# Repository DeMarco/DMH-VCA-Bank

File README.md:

# DMH-VCA-Bank
Another attempt at multiple VCAs in a small module

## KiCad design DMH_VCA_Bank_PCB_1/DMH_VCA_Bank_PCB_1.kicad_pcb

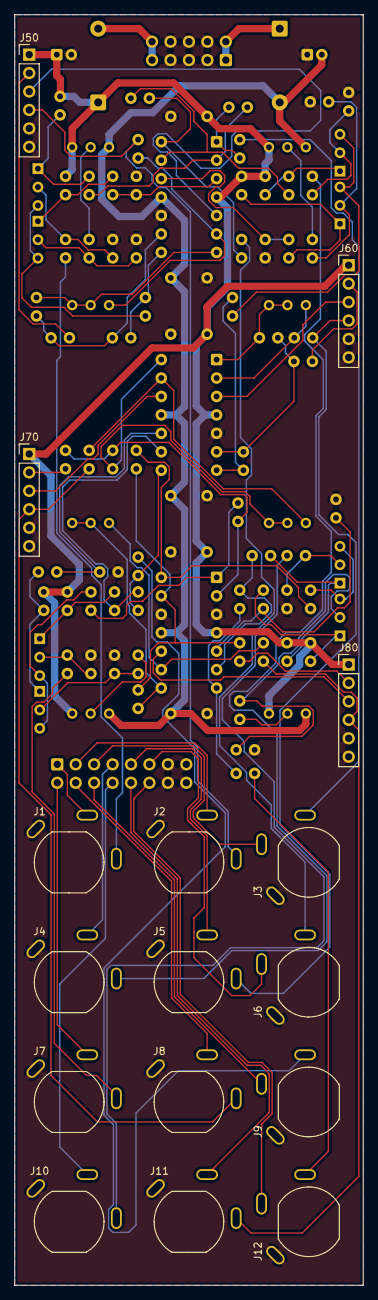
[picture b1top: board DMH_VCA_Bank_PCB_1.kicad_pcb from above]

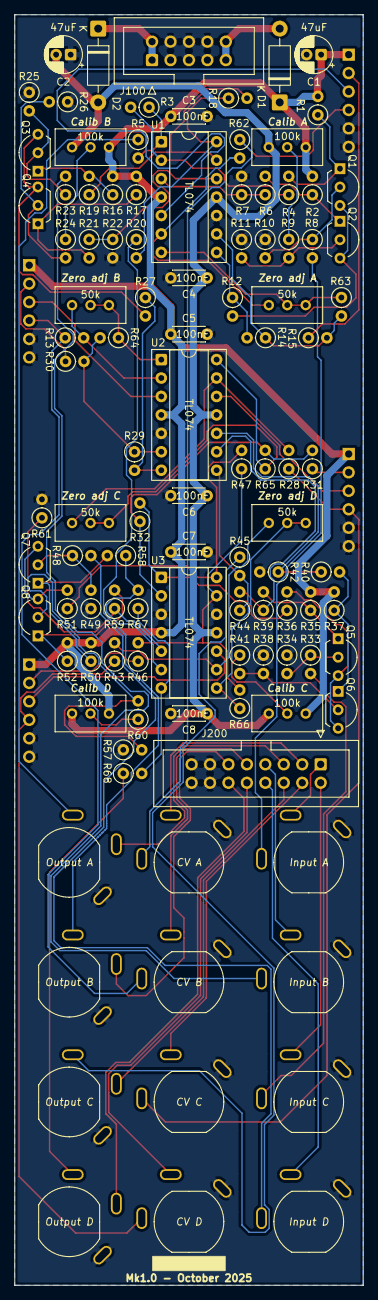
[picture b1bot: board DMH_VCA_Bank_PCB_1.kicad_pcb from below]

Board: 2 copper layers, 48.0 x 175.0 mm, 111 parts (95 on the bottom side), 89 nets.

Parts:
C1, C2: 47uF; CP_Radial_D5.0mm_P2.00mm
C3, C4, C5, C6, C7, C8: 100nF; C_Disc_D4.3mm_W1.9mm_P5.00mm
D1, D2: SB140; D_DO-41_SOD81_P10.16mm_Horizontal
J1, J2, J3, J4, J5, J6, J7, J8, J9, J10, J11, J12: TS_Jack_6.35mm_Sw; CUI_MJ-63052A
J50, J60, J70, J80: Conn_01x06; PinHeader_1x06_P2.54mm_Vertical
J100: IDC_02x05; IDC-Header_2x05_P2.54mm_Vertical_Eurorack
J200: IDC_02x08; IDC-Header_2x08_P2.54mm_Vertical_BackBone
Q1, Q2, Q3, Q4, Q5, Q6, Q7, Q8: BC548; TO-92L_Inline_Wide
R1, R2, R16, R17, R35, R37, R50, R52: 20k; R_Axial_DIN0207_L6.3mm_D2.5mm_P2.54mm_Vertical
R3, R7, R8, R9, R14, R15, R18, R22, R23, R24, R29, R30, R31, R32, R33, R41, R42, R44, R46, R47, R48, R60, R61, R63, R64, R65, R66, R67: 100k; R_Axial_DIN0207_L6.3mm_D2.5mm_P2.54mm_Vertical
R4, R6, R12, R19, R21, R27, R36, R39, R40, R51, R58, R59: 10k; R_Axial_DIN0207_L6.3mm_D2.5mm_P2.54mm_Vertical
R5, R20, R45, R68: 1k; R_Axial_DIN0207_L6.3mm_D2.5mm_P2.54mm_Vertical
R10, R11, R25, R26, R34, R38, R49, R57: 100R; R_Axial_DIN0207_L6.3mm_D2.5mm_P2.54mm_Vertical
R13, R28, R43, R62: 33k; R_Axial_DIN0207_L6.3mm_D2.5mm_P2.54mm_Vertical
RV1, RV2, RV3, RV16: 100k; Potentiometer_Bourns_3296W_Vertical
RV10, RV11, RV12, RV15: 50k; Potentiometer_Bourns_3296W_Vertical
U1, U2, U3: TL074; DIP-14_W7.62mm_Socket

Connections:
+12V: C1.1, C3.1, C5.1, C7.1, D1.1 (K), J50.1, J60.1, J70.1, J80.1, R1.2, R2.2, R16.2, R17.2, R35.2, R37.2, R50.2, R52.2, RV1.3, RV2.3, RV3.3, RV16.3, U1.4 (V+), U2.4 (V+), U3.4 (V+)
-12V: C2.2, C4.2, C6.2, C8.2, D2.2 (A), RV1.1, RV2.1, RV3.1, RV16.1, U1.11 (V-), U2.11 (V-), U3.11 (V-)
/Inputs and Outputs/CV A Jack: J2.T, J50.4, R62.1
/Inputs and Outputs/CV Amt A Pot: J50.3, U1.5 (+)
/Inputs and Outputs/CV Amt B Pot: J60.3, U2.3 (+)
/Inputs and Outputs/CV Amt C Pot: J70.3, U2.12 (+)
/Inputs and Outputs/CV Amt D Pot: J80.3, U3.10 (+)
/Inputs and Outputs/CV B Jack: J5.T, J60.4, R13.1
/Inputs and Outputs/CV C Jack: J8.T, J70.4, R28.1
/Inputs and Outputs/CV D Jack: J11.T, J80.4, R43.1
/Inputs and Outputs/Input A Jack: J1.T, R8.2
/Inputs and Outputs/Input B Jack: J4.T, R23.2
/Inputs and Outputs/Input C Jack: J7.T, R33.2
/Inputs and Outputs/Input D Jack: J10.T, R48.2
/Inputs and Outputs/Offset A Pot: J50.2, R15.1
/Inputs and Outputs/Offset B Pot: J60.2, R30.1
/Inputs and Outputs/Offset C Pot: J70.2, R31.1
/Inputs and Outputs/Offset D Pot: J80.2, R46.1
/Inputs and Outputs/Output A Jack: J3.T, R5.1
/Inputs and Outputs/Output B Jack: J6.T, R20.1
/Inputs and Outputs/Output C Jack: J9.T, R45.1
/Inputs and Outputs/Output D Jack: J12.T, R68.1
GND: C1.2, C2.1, C3.2, C4.1, C5.2, C6.1, C7.2, C8.1, J1.S, J2.S, J3.S, J4.S, J5.S, J6.S, J7.S, J8.S, J9.S, J10.S, J11.S, J12.S, J50.5, J50.6, J60.5, J60.6, J70.5, J70.6, J80.5, J80.6, J100.2a, J100.2b, J100.3a, J100.3b, J100.4a, J100.4b, J200.7, J200.8, J200.15, J200.16, R7.2, R10.1, R11.1, R22.2, R25.1, R26.1, R34.1, R38.1, R42.2, R49.1, R57.1, R61.2, U1.10 (+), U2.5 (+), U3.3 (+), U3.12 (+)
unnamed: D1.2 (A), J100.5a, J100.5b
unnamed: D2.1 (K), J100.1a, J100.1b
unnamed: J1.TN, J200.1
unnamed: J2.TN, J200.2
unnamed: J3.TN, J200.3
unnamed: J4.TN, J200.4
unnamed: J5.TN, J200.5
unnamed: J6.TN, J200.6
unnamed: J7.TN, J200.9
unnamed: J8.TN, J200.10
unnamed: J9.TN, J200.11
unnamed: J10.TN, J200.12
unnamed: J11.TN, J200.13
unnamed: J12.TN, J200.14
unnamed: Q1.2 (B), R8.1, R10.2
unnamed: Q1.1 (C), R1.1, R4.2
unnamed: Q1.3 (E), Q2.3 (E), R12.2
unnamed: Q2.2 (B), R9.2, R11.2
unnamed: Q2.1 (C), R2.1, R6.2
unnamed: Q3.2 (B), R23.1, R25.2
unnamed: Q3.1 (C), R16.1, R19.2
unnamed: Q3.3 (E), Q4.3 (E), R27.2
unnamed: Q4.2 (B), R24.2, R26.2
unnamed: Q4.1 (C), R17.1, R21.2
unnamed: Q5.2 (B), R33.1, R34.2
unnamed: Q5.1 (C), R35.1, R39.2
unnamed: Q5.3 (E), Q6.3 (E), R36.2
unnamed: Q6.2 (B), R38.2, R41.2
unnamed: Q6.1 (C), R37.1, R40.2
unnamed: Q7.2 (B), R48.1, R49.2
unnamed: Q7.1 (C), R50.1, R58.2
unnamed: Q7.3 (E), Q8.3 (E), R51.2
unnamed: Q8.2 (B), R57.2, R60.2
unnamed: Q8.1 (C), R52.1, R59.2
unnamed: R3.1, R5.2, U1.1
unnamed: R9.1, RV1.2
unnamed: R12.1, R14.2, U1.8
unnamed: R18.1, R20.2, U1.14
unnamed: R24.1, RV2.2
unnamed: R27.1, R29.2, U2.7
unnamed: R32.2, R36.1, U3.1
unnamed: R41.1, RV3.2
unnamed: R44.1, R45.2, U2.8
unnamed: R47.2, R51.1, U3.14
unnamed: R60.1, RV16.2
unnamed: R63.1, RV10.2, RV10.3, U1.7
unnamed: R64.1, RV11.2, RV11.3, U2.1
unnamed: R65.1, RV12.2, RV12.3, U2.14
unnamed: R66.1, RV15.2, RV15.3, U3.8
unnamed: R67.1, R68.2, U3.7
unnamed: R6.1, R7.1, U1.3 (+)
unnamed: R3.2, R4.1, U1.2 (-)
unnamed: R62.2, RV10.1, U1.6 (-)
unnamed: R14.1, R15.2, R63.2, U1.9 (-)
unnamed: R21.1, R22.1, U1.12 (+)
unnamed: R18.2, R19.1, U1.13 (-)
unnamed: R13.2, RV11.1, U2.2 (-)
unnamed: R29.1, R30.2, R64.2, U2.6 (-)
unnamed: R40.1, R42.1, U2.10 (+)
unnamed: R39.1, R44.2, U2.9 (-)
unnamed: R28.2, RV12.1, U2.13 (-)
unnamed: R31.2, R32.1, R65.2, U3.2 (-)
unnamed: R59.1, R61.1, U3.5 (+)
unnamed: R58.1, R67.2, U3.6 (-)
unnamed: R43.2, RV15.1, U3.9 (-)
unnamed: R46.2, R47.1, R66.2, U3.13 (-)

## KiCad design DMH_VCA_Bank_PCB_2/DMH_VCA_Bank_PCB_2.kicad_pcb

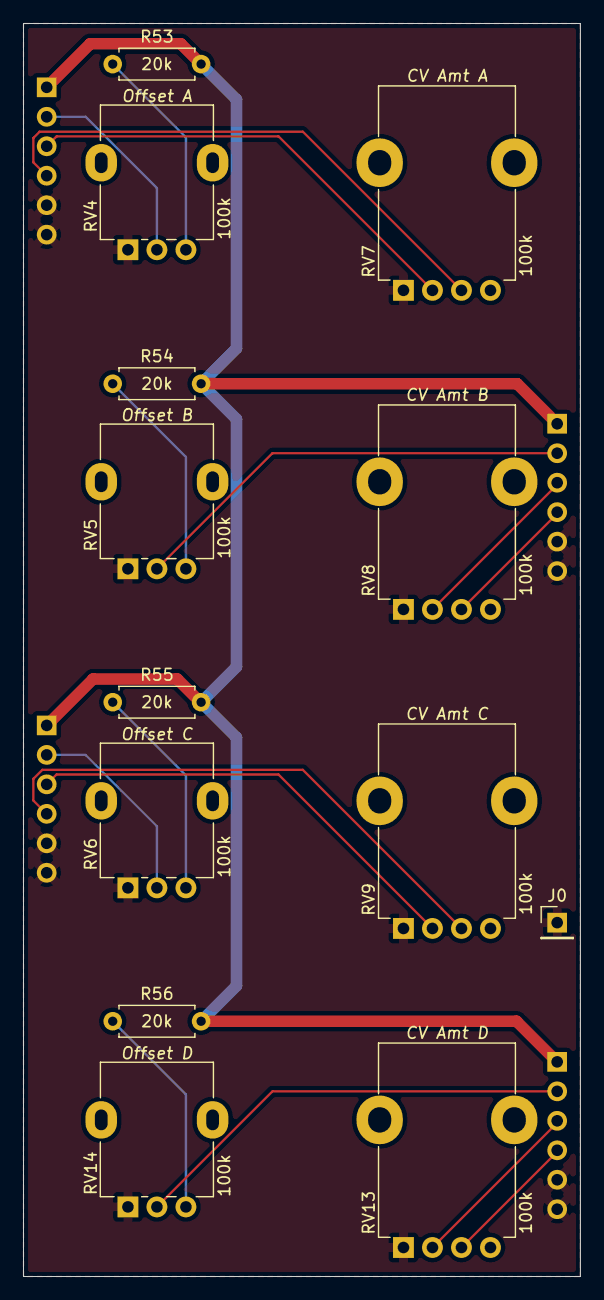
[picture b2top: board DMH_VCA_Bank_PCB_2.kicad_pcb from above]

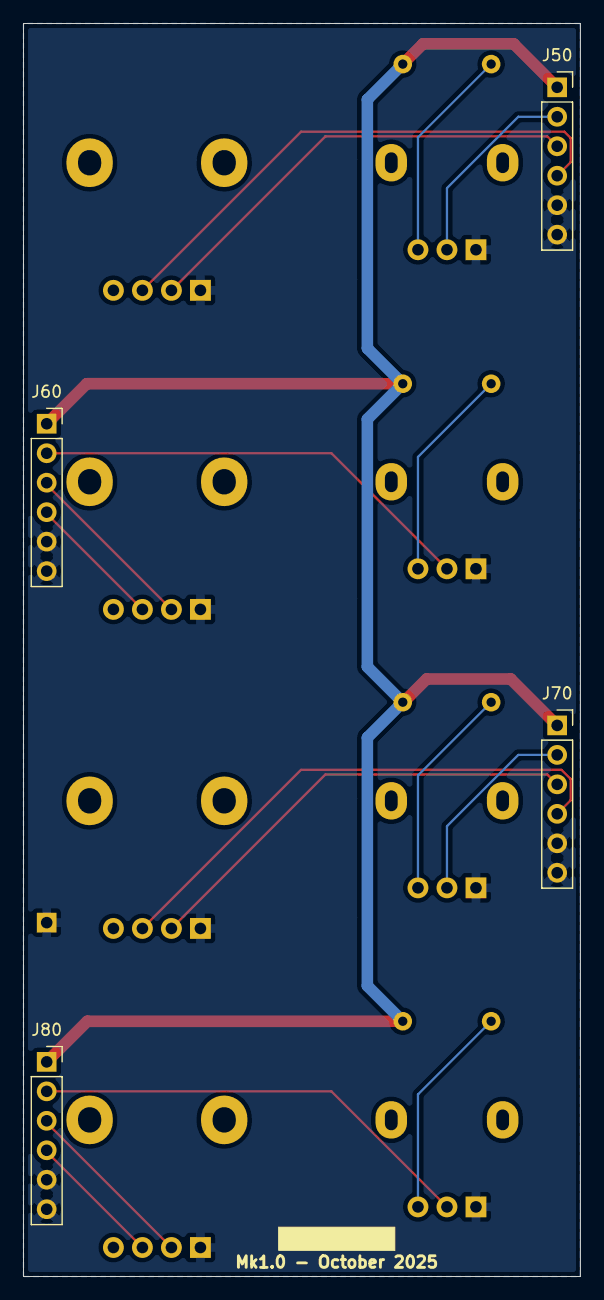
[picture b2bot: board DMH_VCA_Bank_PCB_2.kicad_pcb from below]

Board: 2 copper layers, 48.0 x 108.0 mm, 17 parts (4 on the bottom side), 18 nets.

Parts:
J0: Conn_01x01; PinHeader_1x01_P2.54mm_Vertical
J50, J60, J70, J80: Conn_01x06; PinSocket_1x06_P2.54mm_Vertical
R53, R54, R55, R56: 20k; R_Axial_DIN0207_L6.3mm_D2.5mm_P7.62mm_Horizontal
RV4, RV5, RV6, RV14: 100k; Potentiometer_Alpha_RD901F-40-00D_Single_Vertical
RV7, RV8, RV9, RV13: 100k; Potentiometer_TT_P110KH1

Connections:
+12V: J50.1, J60.1, J70.1, J80.1, R53.2, R54.2, R55.2, R56.2
/Inputs and Outputs/CV A Jack: J50.4, RV7.3
/Inputs and Outputs/CV Amt A Pot: J50.3, RV7.2
/Inputs and Outputs/CV Amt B Pot: J60.3, RV8.2
/Inputs and Outputs/CV Amt C Pot: J70.3, RV9.2
/Inputs and Outputs/CV Amt D Pot: J80.3, RV13.2
/Inputs and Outputs/CV B Jack: J60.4, RV8.3
/Inputs and Outputs/CV C Jack: J70.4, RV9.3
/Inputs and Outputs/CV D Jack: J80.4, RV13.3
/Inputs and Outputs/Offset A Pot: J50.2, RV4.2
/Inputs and Outputs/Offset B Pot: J60.2, RV5.2
/Inputs and Outputs/Offset C Pot: J70.2, RV6.2
/Inputs and Outputs/Offset D Pot: J80.2, RV14.2
GND: J0.1 (Pin_1_1), J50.5, J50.6, J60.5, J60.6, J70.5, J70.6, J80.5, J80.6, RV4.1, RV5.1, RV6.1, RV7.1, RV8.1, RV9.1, RV13.1, RV14.1
unnamed: R53.1, RV4.3
unnamed: R54.1, RV5.3
unnamed: R55.1, RV6.3
unnamed: R56.1, RV14.3

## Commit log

2025-04-24 Created PANEL project
2025-04-25 Panel ready
2025-07-05 Started PCB 1 and 2 projects based on VCM Mk2
2025-07-05 Finished schematic of PCB 1
2025-07-05 Finished schematic of PCB 2
2025-07-05 Finished PCB 2
2025-07-05 PCB 1 placement started
2025-07-06 PCB 1 component placement in progress
2025-07-07 PCB 1 component placement done
2025-07-07 Routing in progress
2025-07-09 Routing done but needs error correction
2025-07-10 All PCB 1 errors solved
2025-07-10 PCB 1 Optimized
2025-10-04 Generated Gerbers
2025-10-15 Made resistor values visible in PCB
2026-06-13 KiCad 10 and updated SynthStuff
2026-06-20 Experimenting with design blocks
